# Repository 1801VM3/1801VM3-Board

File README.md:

# 1801VM3-Board
# 1801VM3-Board

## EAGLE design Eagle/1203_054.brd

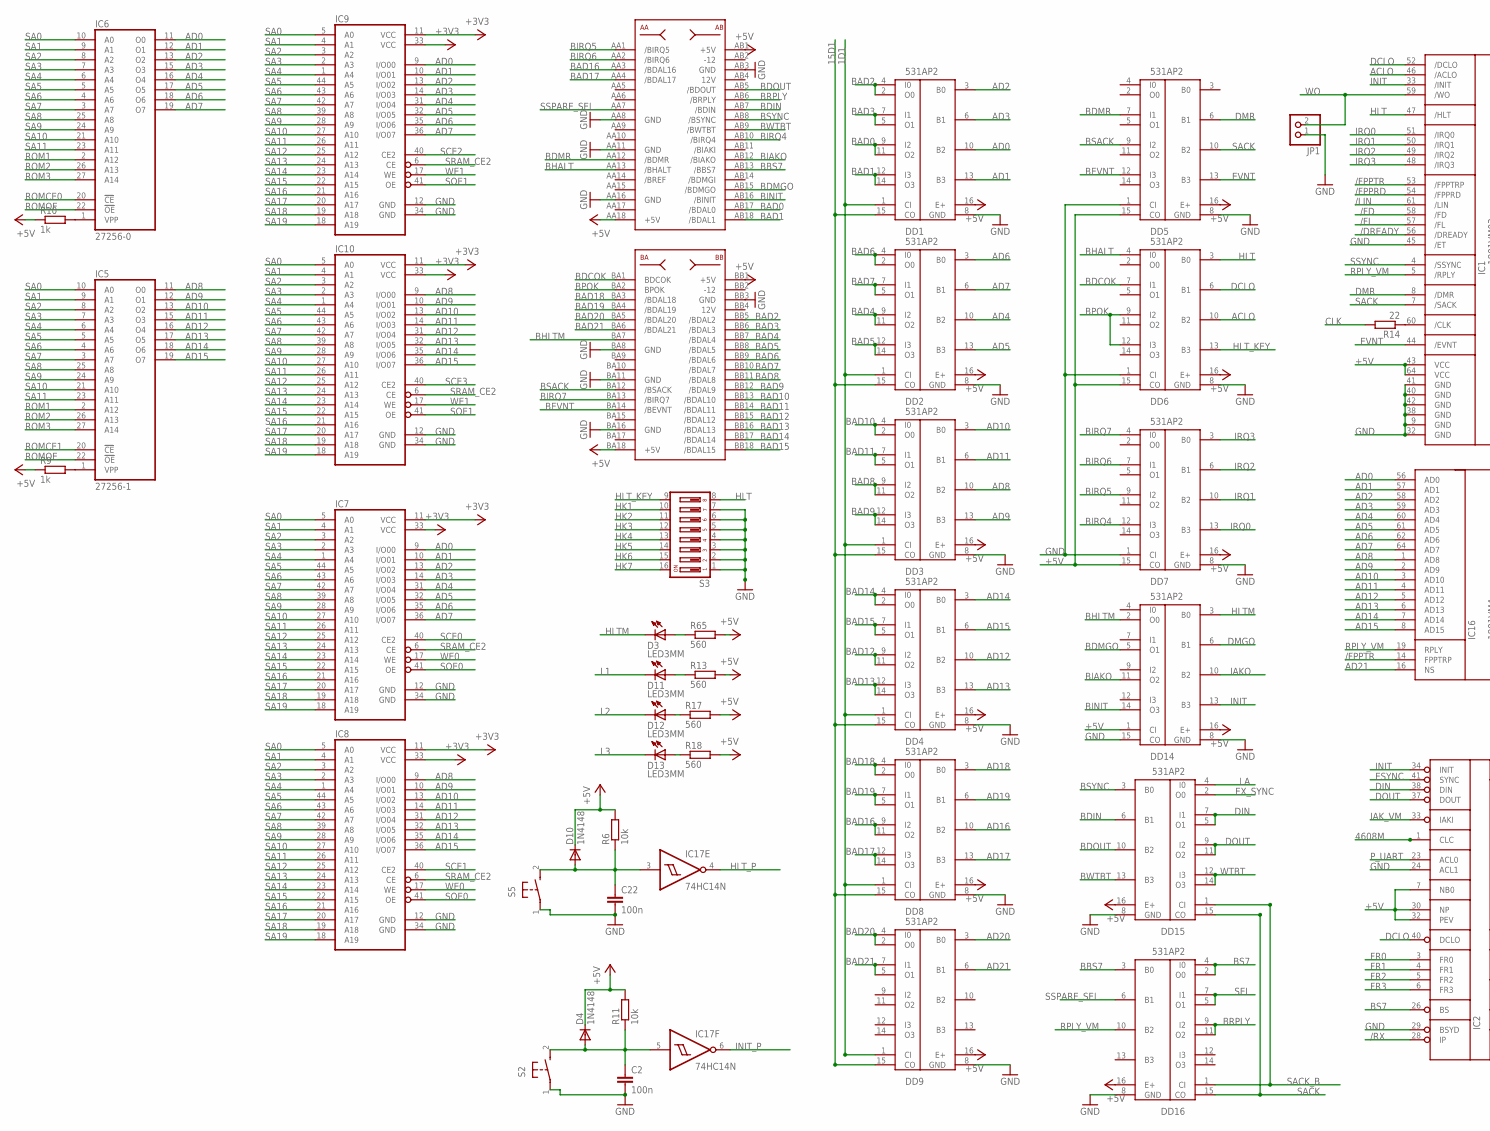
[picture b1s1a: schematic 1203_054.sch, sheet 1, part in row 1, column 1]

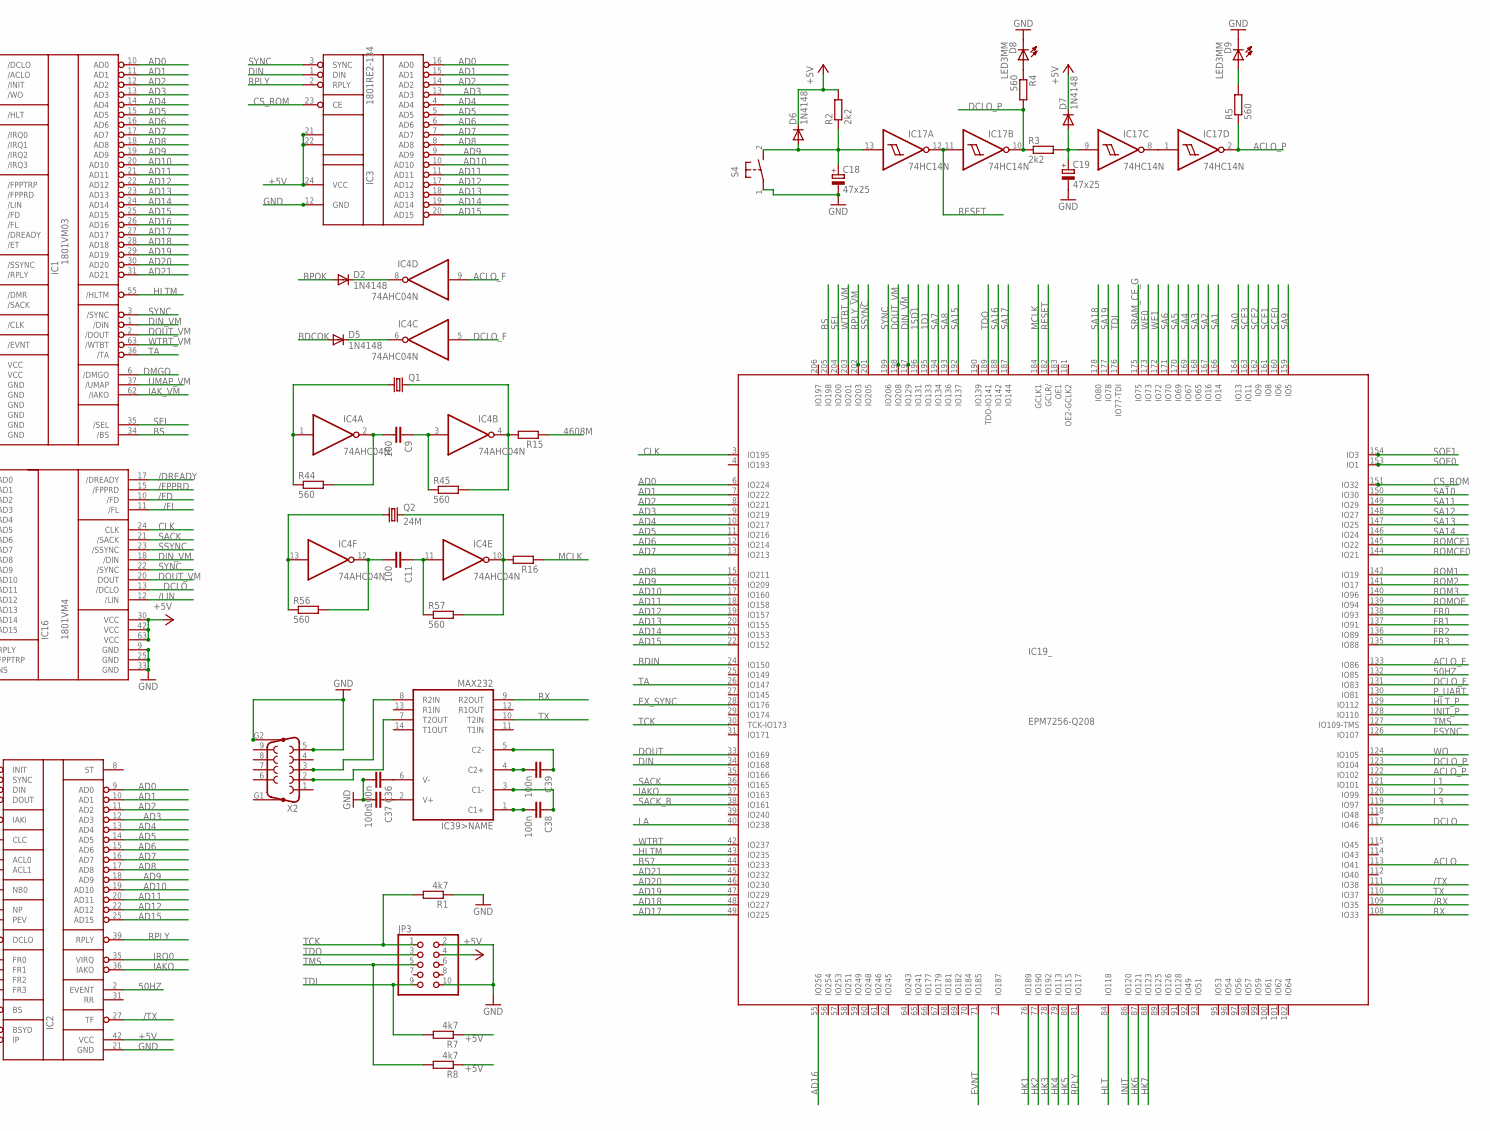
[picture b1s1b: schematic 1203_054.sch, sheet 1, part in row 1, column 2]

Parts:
C2, C22: 100n; C050-024X044
C9, C11: 100; C025-024X044
C18, C19: 47x25; E2,5-5
C36, C37, C38, C39: 100n; C025-024X044
D2, D4, D5, D6, D7, D10: 1N4148; DO35-10
D3, D8, D9, D11, D12, D13: LED3MM
DD1, DD2, DD3, DD4, DD5, DD6, DD7, DD8, DD9, DD14, DD15, DD16: 531AP2; DIL16
IC1: 1801VM03; DIL64
IC2: 1801VP1-065; 1801
IC3: 1801RE2-134; DIL24
IC4: 74AHC04N; DIL14
IC5: 27256-1; DIL28
IC6: 27256-0; DIL28
IC7, IC8, IC9, IC10: AS6C800855Z; TSOP44
IC16: 1801VM4
IC17: 74HC14N; DIL14
IC19: EPM7256-Q208; RQFP208
IC39: MAX232; DIL16
JP1: PINHD-1X2; 1X02
JP3: PINHD-2X5; 2X05
Q1: HC49U70
Q2: 24M; HC49U70
R1, R7, R8: 4k7; M0805
R2, R3: 2k2; 0207/10
R4, R5, R13, R17, R18, R65: 560; M0805
R6, R11: 10k; 0207/10
R9, R10: 1k; M0805
R14: 22; 0204V
R15, R16: R-EU_0204/2V; 0204V
R44, R45, R56, R57: 560; 0204V
S2, S4, S5: 31-XX; B3F-31XX
S3: DP08; DP-08
X2: F09HP
XP1: CON1

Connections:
1D1: DD1.1 (CI), DD2.1 (CI), DD3.1 (CI), DD4.1 (CI), DD8.1 (CI), DD9.1 (CI), IC19.195 (IO133); also elsewhere on the board
15D1: DD1.15 (CO), DD2.15 (CO), DD3.15 (CO), DD4.15 (CO), DD8.15 (CO), DD9.15 (CO), IC19.196 (IO131)
50HZ: IC2.2 (EVENT), IC19.132 (IO85)
4608M: IC2.1 (CLC), R15.1
4608MM: IC4.10 (O), Q2.2, R16.2, R57.2
+3V3: IC7.11 (VCC), IC7.33 (VCC), IC8.11 (VCC), IC8.33 (VCC), IC9.11 (VCC), IC9.33 (VCC), IC10.11 (VCC), IC10.33 (VCC); also elsewhere on the board
+5V: D4.K (C), D6.K (C), D7.K (C), D10.K (C), DD1.16 (E+), DD2.16 (E+), DD3.16 (E+), DD4.16 (E+), DD5.15 (CO), DD5.16 (E+), DD6.15 (CO), DD6.16 (E+), DD7.15 (CO), DD7.16 (E+), DD8.16 (E+), DD9.16 (E+), DD14.1 (CI), DD14.16 (E+), DD15.16 (E+), DD16.16 (E+), IC1.43 (VCC), IC1.64 (VCC), IC2.7 (NB0), IC2.30 (NP), IC2.32 (PEV), IC2.42 (VCC), IC3.21 (F0), IC3.22 (F1), IC3.24 (VCC), IC4.14 (VCC), IC5.28 (VCC), IC6.28 (VCC), IC16.30 (VCC), IC16.42 (VCC), IC16.63 (VCC), IC17.14 (VCC), IC19.83 (VCC), IC19.179 (VCC), IC19.186 (VCC), JP3.4, R2.2, R6.2, R7.1, R8.1, R9.1, R10.1, R11.2, R13.2, R17.2, R18.2, R65.2, XP1.AA18 (+5V), XP1.AB1 (+5V), XP1.BA18 (+5V), XP1.BB1 (+5V); also elsewhere on the board
/DREADY: IC1.56 (/DREADY), IC16.17 (/DREADY); also elsewhere on the board
/FD: IC1.58 (/FD), IC16.10 (/FD); also elsewhere on the board
/FL: IC1.57 (/FL), IC16.11 (/FL); also elsewhere on the board
/FPPRD: IC1.54 (/FPPRD), IC16.15 (/FPPRD); also elsewhere on the board
/FPPTR: IC1.53 (/FPPTRP), IC16.14 (FPPTRP); also elsewhere on the board
/LIN: IC1.61 (/LIN), IC16.12 (/LIN); also elsewhere on the board
/RX: IC2.28 (IP), IC19.109 (IO35)
/TX: IC2.27 (TF), IC19.111 (IO38)
ACLO: DD6.10 (B2), IC1.46 (/ACLO), IC19.113 (IO41); also elsewhere on the board
ACLO_F: IC4.9 (I), IC19.133 (IO86)
ACLO_P: IC17.2 (O), IC19.122 (IO102), R5.1
AD0: DD1.10 (B2), IC1.10 (AD0), IC2.9 (AD0), IC3.16 (AD0), IC6.11 (O0), IC7.9 (I/O00), IC9.9 (I/O00), IC16.56 (AD0), IC19.6 (IO224); also elsewhere on the board
AD1: DD1.13 (B3), IC1.11 (AD1), IC2.10 (AD1), IC3.15 (AD1), IC6.12 (O1), IC7.10 (I/O01), IC9.10 (I/O01), IC16.57 (AD1), IC19.7 (IO222); also elsewhere on the board
AD2: DD1.3 (B0), IC1.12 (AD2), IC2.11 (AD2), IC3.14 (AD2), IC6.13 (O2), IC7.13 (I/O02), IC9.13 (I/O02), IC16.58 (AD2), IC19.8 (IO221); also elsewhere on the board
AD3: DD1.6 (B1), IC1.13 (AD3), IC2.12 (AD3), IC3.13 (AD3), IC6.15 (O3), IC7.14 (I/O03), IC9.14 (I/O03), IC16.59 (AD3), IC19.9 (IO219); also elsewhere on the board
AD4: DD2.10 (B2), IC1.14 (AD4), IC2.13 (AD4), IC3.4 (AD4), IC6.16 (O4), IC7.31 (I/O04), IC9.31 (I/O04), IC16.60 (AD4), IC19.10 (IO217); also elsewhere on the board
AD5: DD2.13 (B3), IC1.15 (AD5), IC2.14 (AD5), IC3.5 (AD5), IC6.17 (O5), IC7.32 (I/O05), IC9.32 (I/O05), IC16.61 (AD5), IC19.11 (IO216); also elsewhere on the board
AD6: DD2.3 (B0), IC1.16 (AD6), IC2.15 (AD6), IC3.6 (AD6), IC6.18 (O6), IC7.35 (I/O06), IC9.35 (I/O06), IC16.62 (AD6), IC19.12 (IO214); also elsewhere on the board
AD7: DD2.6 (B1), IC1.17 (AD7), IC2.16 (AD7), IC3.7 (AD7), IC6.19 (O7), IC7.36 (I/O07), IC9.36 (I/O07), IC16.64 (AD7), IC19.13 (IO213); also elsewhere on the board
AD8: DD3.10 (B2), IC1.18 (AD8), IC2.17 (AD8), IC3.8 (AD8), IC5.11 (O0), IC8.9 (I/O00), IC10.9 (I/O00), IC16.1 (AD8), IC19.15 (IO211); also elsewhere on the board
AD9: DD3.13 (B3), IC1.19 (AD9), IC2.18 (AD9), IC3.9 (AD9), IC5.12 (O1), IC8.10 (I/O01), IC10.10 (I/O01), IC16.2 (AD9), IC19.16 (IO209); also elsewhere on the board
AD10: DD3.3 (B0), IC1.20 (AD10), IC2.19 (AD10), IC3.10 (AD10), IC5.13 (O2), IC8.13 (I/O02), IC10.13 (I/O02), IC16.3 (AD10), IC19.17 (IO160); also elsewhere on the board
AD11: DD3.6 (B1), IC1.21 (AD11), IC2.20 (AD11), IC3.11 (AD11), IC5.15 (O3), IC8.14 (I/O03), IC10.14 (I/O03), IC16.4 (AD11), IC19.18 (IO158); also elsewhere on the board
AD12: DD4.10 (B2), IC1.22 (AD12), IC2.22 (AD12), IC3.17 (AD12), IC5.16 (O4), IC8.31 (I/O04), IC10.31 (I/O04), IC16.5 (AD12), IC19.19 (IO157); also elsewhere on the board
AD13: DD4.13 (B3), IC1.23 (AD13), IC3.18 (AD13), IC5.17 (O5), IC8.32 (I/O05), IC10.32 (I/O05), IC16.6 (AD13), IC19.20 (IO155); also elsewhere on the board
AD14: DD4.3 (B0), IC1.24 (AD14), IC3.19 (AD14), IC5.18 (O6), IC8.35 (I/O06), IC10.35 (I/O06), IC16.7 (AD14), IC19.21 (IO153); also elsewhere on the board
AD15: DD4.6 (B1), IC1.25 (AD15), IC2.25 (AD15), IC3.20 (AD15), IC5.19 (O7), IC8.36 (I/O07), IC10.36 (I/O07), IC16.8 (AD15), IC19.22 (IO152); also elsewhere on the board
AD16: DD8.10 (B2), IC1.26 (AD16), IC19.55 (IO256); also elsewhere on the board
AD17: DD8.13 (B3), IC1.27 (AD17), IC19.49 (IO225); also elsewhere on the board
AD18: DD8.3 (B0), IC1.28 (AD18), IC19.48 (IO227); also elsewhere on the board
AD19: DD8.6 (B1), IC1.29 (AD19), IC19.47 (IO229); also elsewhere on the board
AD20: DD9.3 (B0), IC1.30 (AD20), IC19.46 (IO230); also elsewhere on the board
AD21: DD9.6 (B1), IC1.31 (AD21), IC16.16 (NS), IC19.45 (IO232); also elsewhere on the board
BAD0: DD1.9 (I2), DD1.11 (O2), XP1.AB17 (/BDAL0); also elsewhere on the board
BAD1: DD1.12 (I3), DD1.14 (O3), XP1.AB18 (/BDAL1); also elsewhere on the board
BAD2: DD1.2 (O0), DD1.4 (I0), XP1.BB5 (/BDAL2); also elsewhere on the board
BAD3: DD1.5 (O1), DD1.7 (I1), XP1.BB6 (/BDAL3); also elsewhere on the board
BAD4: DD2.9 (I2), DD2.11 (O2), XP1.BB7 (/BDAL4); also elsewhere on the board
BAD5: DD2.12 (I3), DD2.14 (O3), XP1.BB8 (/BDAL5); also elsewhere on the board
BAD6: DD2.2 (O0), DD2.4 (I0), XP1.BB9 (/BDAL6); also elsewhere on the board
BAD7: DD2.5 (O1), DD2.7 (I1), XP1.BB10 (/BDAL7); also elsewhere on the board
BAD8: DD3.9 (I2), DD3.11 (O2), XP1.BB11 (/BDAL8); also elsewhere on the board
BAD9: DD3.12 (I3), DD3.14 (O3), XP1.BB12 (/BDAL9); also elsewhere on the board
BAD10: DD3.2 (O0), DD3.4 (I0), XP1.BB13 (/BDAL10); also elsewhere on the board
BAD11: DD3.5 (O1), DD3.7 (I1), XP1.BB14 (/BDAL11); also elsewhere on the board
BAD12: DD4.9 (I2), DD4.11 (O2), XP1.BB15 (/BDAL12); also elsewhere on the board
BAD13: DD4.12 (I3), DD4.14 (O3), XP1.BB16 (/BDAL13); also elsewhere on the board
BAD14: DD4.2 (O0), DD4.4 (I0), XP1.BB17 (/BDAL14); also elsewhere on the board
BAD15: DD4.5 (O1), DD4.7 (I1), XP1.BB18 (/BDAL15); also elsewhere on the board
BAD16: DD8.9 (I2), DD8.11 (O2), XP1.AA3 (/BDAL16); also elsewhere on the board
BAD17: DD8.12 (I3), DD8.14 (O3), XP1.AA4 (/BDAL17); also elsewhere on the board
BAD18: DD8.2 (O0), DD8.4 (I0), XP1.BA3 (/BDAL18); also elsewhere on the board
BAD19: DD8.5 (O1), DD8.7 (I1), XP1.BA4 (/BDAL19); also elsewhere on the board
BAD20: DD9.2 (O0), DD9.4 (I0), XP1.BA5 (/BDAL20); also elsewhere on the board
BAD21: DD9.5 (O1), DD9.7 (I1), XP1.BA6 (/BDAL21); also elsewhere on the board
BBS7: DD16.3 (B0), XP1.AB13 (/BBS7); also elsewhere on the board
BDCOK: D5.A, DD6.7 (I1), XP1.BA1 (BDCOK); also elsewhere on the board
BDIN: DD15.6 (B1), IC19.24 (IO150), XP1.AB7 (/BDIN); also elsewhere on the board
BDMGO: DD14.5 (O1), XP1.AB15 (/BDMGO); also elsewhere on the board
BDMR: DD5.7 (I1), XP1.AA12 (/BDMR); also elsewhere on the board
BDOUT: DD15.10 (B2), XP1.AB5 (/BDOUT); also elsewhere on the board
BEVNT: DD5.12 (I3), XP1.BA14 (/BEVNT); also elsewhere on the board
BHALT: DD6.4 (I0), XP1.AA13 (/BHALT); also elsewhere on the board
BHLTM: DD14.2 (O0), XP1.BA7; also elsewhere on the board
BIAKO: DD14.11 (O2), XP1.AB12 (/BIAKO); also elsewhere on the board
BINIT: DD14.14 (O3), XP1.AB16 (/BINIT); also elsewhere on the board
BIRQ4: DD7.12 (I3), XP1.AB10 (/BIRQ4); also elsewhere on the board
BIRQ5: DD7.9 (I2), XP1.AA1 (/BIRQ5); also elsewhere on the board
BIRQ6: DD7.7 (I1), XP1.AA2 (/BIRQ6); also elsewhere on the board
BIRQ7: DD7.4 (I0), XP1.BA13 (/BIRQ7); also elsewhere on the board
BPOK: D2.A, DD6.9 (I2), DD6.12 (I3), XP1.BA2 (BPOK); also elsewhere on the board
BRPLY: DD16.9 (I2), DD16.11 (O2), XP1.AB6 (/BRPLY); also elsewhere on the board
BS: IC1.34 (/BS), IC19.205 (IO198); also elsewhere on the board
BS7: DD16.2 (O0), DD16.4 (I0), IC2.26 (BS), IC19.44 (IO233); also elsewhere on the board
BSACK: DD5.9 (I2), XP1.BA12 (/BSACK); also elsewhere on the board
BSYNC: DD15.3 (B0), XP1.AB8 (/BSYNC); also elsewhere on the board
BWTBT: DD15.13 (B3), XP1.AB9 (/BWTBT); also elsewhere on the board
CLK: IC16.24 (CLK), IC19.3 (IO195), R14.2
CS_ROM: IC3.23 (CE), IC19.151 (IO32)
DCLO: DD6.6 (B1), IC1.52 (/DCLO), IC2.40 (DCLO), IC16.13 (/DCLO), IC19.117 (IO46); also elsewhere on the board
DCLO_F: IC4.5 (I), IC19.131 (IO83)
DCLO_P: IC17.10 (O), IC19.123 (IO104), R3.1, R4.2
DIN: DD15.5 (O1), DD15.7 (I1), IC2.38 (DIN), IC3.1 (DIN), IC19.34 (IO168); also elsewhere on the board
DIN_VM: IC1.1 (/DIN), IC16.18 (/DIN), IC19.197 (IO129); also elsewhere on the board
DMGO: DD14.6 (B1), IC1.6 (/DMGO); also elsewhere on the board
DMR: DD5.6 (B1), IC1.8 (/DMR); also elsewhere on the board
DOUT: DD15.9 (I2), DD15.11 (O2), IC2.37 (DOUT), IC19.33 (IO169); also elsewhere on the board
DOUT_VM: IC1.2 (/DOUT), IC16.20 (DOUT), IC19.198 (IO208); also elsewhere on the board
ESYNC: IC2.41 (SYNC), IC19.126 (IO107)
EVNT: DD5.13 (B3), IC1.44 (/EVNT), IC19.71 (IO185); also elsewhere on the board
EX_SYNC: DD15.2 (O0), IC19.28 (IO176); also elsewhere on the board
FR0: IC2.3 (FR0), IC19.138 (IO93)
FR1: IC2.4 (FR1), IC19.137 (IO91)
FR2: IC2.5 (FR2), IC19.136 (IO89)
FR3: IC2.6 (FR3), IC19.135 (IO88)
GND: C2.2, C18.-, C19.-, C22.2, C36.2, C37.2, D8.K (C), D9.K (C), DD1.8 (GND), DD2.8 (GND), DD3.8 (GND), DD4.8 (GND), DD5.1 (CI), DD5.8 (GND), DD6.1 (CI), DD6.8 (GND), DD7.1 (CI), DD7.8 (GND), DD8.8 (GND), DD9.8 (GND), DD14.8 (GND), DD14.15 (CO), DD15.8 (GND), DD16.8 (GND), IC1.9 (GND), IC1.32 (GND), IC1.38 (GND), IC1.40 (GND), IC1.41 (GND), IC1.42 (GND), IC1.45 (/ET), IC2.21 (GND), IC2.24 (ACL1), IC2.29 (BSYD), IC3.12 (GND), IC4.7 (GND), IC5.14 (GND), IC6.14 (GND), IC7.12 (GND), IC7.34 (GND), IC8.12 (GND), IC8.34 (GND), IC9.12 (GND), IC9.34 (GND), IC10.12 (GND), IC10.34 (GND), IC16.9 (GND), IC16.25 (GND), IC16.33 (GND), IC17.7 (GND), JP1.1, JP3.2, JP3.10, R1.1, S2.1, S3.1, S3.2, S3.3, S3.4, S3.5, S3.6, S3.7, S4.1, S5.1, X2.5, X2.G2, XP1.AA8 (GND), XP1.AA11 (GND), XP1.AA16 (GND), XP1.AB3 (GND), XP1.BA8 (GND), XP1.BA11 (GND), XP1.BA16 (GND), XP1.BB3 (GND); also elsewhere on the board
HK1: IC19.76 (IO189), S3.10; also elsewhere on the board
HK2: IC19.77 (IO190), S3.11; also elsewhere on the board
HK3: IC19.78 (IO192), S3.12; also elsewhere on the board
HK4: IC19.79 (IO113), S3.13; also elsewhere on the board
HK5: IC19.80 (IO115), S3.14; also elsewhere on the board
HK6: IC19.87 (IO121), S3.15; also elsewhere on the board
HK7: IC19.88 (IO123), S3.16; also elsewhere on the board
HLT: DD6.3 (B0), IC1.47 (/HLT), IC19.84 (IO118), S3.8; also elsewhere on the board
HLTM: D3.K (C), DD14.3 (B0), IC1.55 (/HLTM), IC19.43 (IO235); also elsewhere on the board
HLT_KEY: DD6.13 (B3), S3.9
HLT_P: IC17.4 (O), IC19.129 (IO112)
IAKO: DD14.10 (B2), IC2.36 (IAKO), IC19.37 (IO163)
IAK_VM: IC1.62 (/IAKO), IC2.33 (IAKI); also elsewhere on the board
INIT: DD14.13 (B3), IC1.33 (/INIT), IC2.34 (INIT), IC19.86 (IO120); also elsewhere on the board
INIT_P: IC17.6 (O), IC19.128 (IO110)
IRQ0: DD7.13 (B3), IC1.51 (/IRQ0), IC2.35 (VIRQ); also elsewhere on the board
IRQ1: DD7.10 (B2), IC1.50 (/IRQ1); also elsewhere on the board
IRQ2: DD7.6 (B1), IC1.49 (/IRQ2); also elsewhere on the board
IRQ3: DD7.3 (B0), IC1.48 (/IRQ3); also elsewhere on the board
L1: D11.K (C), IC19.121 (IO101)
L2: D12.K (C), IC19.120 (IO99)
L3: D13.K (C), IC19.119 (IO97)
LA: DD15.4 (I0), IC19.40 (IO238)
MCLK: IC19.184 (GCLK1), R16.1
MCLKK: IC4.4 (O), Q1.2, R15.2, R45.2
unnamed: IC6.1 (VPP), R10.2
unnamed: IC17.1 (I), IC17.8 (O)
unnamed: C38.1, IC39.3 (C1-)
unnamed: D9.A, R5.2
unnamed: C18.+, D6.A, IC17.13 (I), R2.1, S4.2
unnamed: IC4.1 (I), Q1.1, R44.1
unnamed: D3.A, R65.1
unnamed: C9.2, IC4.2 (O), R44.2
unnamed: C19.+, D7.A, IC17.9 (I), R3.2
unnamed: D8.A, R4.1
unnamed: IC5.1 (VPP), R9.2
unnamed: C22.1, D10.A, IC17.3 (I), R6.1, S5.2
unnamed: D11.A, R13.1
unnamed: IC1.60 (/CLK), R14.1
unnamed: D2.K (C), IC4.8 (O)
unnamed: D5.K (C), IC4.6 (O)
unnamed: C2.1, D4.A, IC17.5 (I), R11.1, S2.2
unnamed: D12.A, R17.1
unnamed: D13.A, R18.1
unnamed: IC4.13 (I), Q2.1, R56.1
unnamed: C9.1, IC4.3 (I), R45.1
unnamed: C38.2, IC39.1 (C1+)
unnamed: C39.2, IC39.4 (C2+)
unnamed: C39.1, IC39.5 (C2-)
unnamed: IC39.7 (T2OUT), X2.2
unnamed: IC39.8 (R2IN), X2.3
unnamed: C36.1, IC39.6 (V-)
unnamed: C37.1, IC39.2 (V+)
unnamed: C11.2, IC4.12 (O), R56.2
unnamed: C11.1, IC4.11 (I), R57.1
P_UART: IC2.23 (ACL0), IC19.130 (IO81)
RESET: IC17.11 (I), IC17.12 (O), IC19.182 (GCLR/)
ROM1: IC5.2 (A12), IC6.2 (A12), IC19.142 (IO19)
ROM2: IC5.26 (A13), IC6.26 (A13), IC19.141 (IO17)
ROM3: IC5.27 (A14), IC6.27 (A14), IC19.140 (IO96)
ROMCE0: IC6.20 (!CE), IC19.144 (IO21)
ROMCE1: IC5.20 (!CE), IC19.145 (IO22)
ROMOE: IC5.22 (!OE), IC6.22 (!OE), IC19.139 (IO94)
RPLY: IC2.39 (RPLY), IC3.2 (RPLY), IC19.81 (IO117); also elsewhere on the board
RPLY_VM: DD16.10 (B2), IC1.5 (/RPLY), IC16.19 (RPLY), IC19.202 (IO203); also elsewhere on the board
RX: IC19.108 (IO33), IC39.9 (R2OUT)
SA0: IC5.10 (A0), IC6.10 (A0), IC7.5 (A0), IC8.5 (A0), IC9.5 (A0), IC10.5 (A0), IC19.164 (IO13)
SA1: IC5.9 (A1), IC6.9 (A1), IC7.4 (A1), IC8.4 (A1), IC9.4 (A1), IC10.4 (A1), IC19.166 (IO14)
SA2: IC5.8 (A2), IC6.8 (A2), IC7.3 (A2), IC8.3 (A2), IC9.3 (A2), IC10.3 (A2), IC19.167 (IO16)
SA3: IC5.7 (A3), IC6.7 (A3), IC7.2 (A3), IC8.2 (A3), IC9.2 (A3), IC10.2 (A3), IC19.168 (IO65)
SA4: IC5.6 (A4), IC6.6 (A4), IC7.1 (A4), IC8.1 (A4), IC9.1 (A4), IC10.1 (A4), IC19.169 (IO67)
SA5: IC5.5 (A5), IC6.5 (A5), IC7.44 (A5), IC8.44 (A5), IC9.44 (A5), IC10.44 (A5), IC19.170 (IO69)
SA6: IC5.4 (A6), IC6.4 (A6), IC7.43 (A6), IC8.43 (A6), IC9.43 (A6), IC10.43 (A6), IC19.171 (IO70)
SA7: IC5.3 (A7), IC6.3 (A7), IC7.42 (A7), IC8.42 (A7), IC9.42 (A7), IC10.42 (A7), IC19.194 (IO134)
SA8: IC5.25 (A8), IC6.25 (A8), IC7.39 (A8), IC8.39 (A8), IC9.39 (A8), IC10.39 (A8), IC19.193 (IO136)
SA9: IC5.24 (A9), IC6.24 (A9), IC7.28 (A9), IC8.28 (A9), IC9.28 (A9), IC10.28 (A9), IC19.159 (IO5)
SA10: IC5.21 (A10), IC6.21 (A10), IC7.27 (A10), IC8.27 (A10), IC9.27 (A10), IC10.27 (A10), IC19.150 (IO30)
SA11: IC5.23 (A11), IC6.23 (A11), IC7.26 (A11), IC8.26 (A11), IC9.26 (A11), IC10.26 (A11), IC19.149 (IO29)
SA12: IC7.25 (A12), IC8.25 (A12), IC9.25 (A12), IC10.25 (A12), IC19.148 (IO27)
SA13: IC7.24 (A13), IC8.24 (A13), IC9.24 (A13), IC10.24 (A13), IC19.147 (IO25)
SA14: IC7.23 (A14), IC8.23 (A14), IC9.23 (A14), IC10.23 (A14), IC19.146 (IO24)
SA15: IC7.22 (A15), IC8.22 (A15), IC9.22 (A15), IC10.22 (A15), IC19.192 (IO137)
SA16: IC7.21 (A16), IC8.21 (A16), IC9.21 (A16), IC10.21 (A16), IC19.188 (IO142)
SA17: IC7.20 (A17), IC8.20 (A17), IC9.20 (A17), IC10.20 (A17), IC19.187 (IO144)
SA18: IC7.19 (A18), IC8.19 (A18), IC9.19 (A18), IC10.19 (A18), IC19.178 (IO80)
SA19: IC7.18 (A19), IC8.18 (A19), IC9.18 (A19), IC10.18 (A19), IC19.177 (IO78)
SACK: DD5.10 (B2), DD15.15 (CO), DD16.15 (CO), IC1.7 (/SACK), IC16.21 (/SACK), IC19.36 (IO165); also elsewhere on the board
SACK_B: DD15.1 (CI), DD16.1 (CI), IC19.38 (IO161)
SCE0: IC7.40 (CE2), IC19.160 (IO6)
SCE1: IC8.40 (CE2), IC19.161 (IO8)
SCE2: IC9.40 (CE2), IC19.162 (IO9)
SCE3: IC10.40 (CE2), IC19.163 (IO11)
SEL: DD16.5 (O1), DD16.7 (I1), IC1.35 (/SEL), IC19.204 (IO200); also elsewhere on the board
SOE0: IC7.41 (OE), IC8.41 (OE), IC19.153 (IO1)
SOE1: IC9.41 (OE), IC10.41 (OE), IC19.154 (IO3)
SRAM_CE2: IC7.6 (CE), IC8.6 (CE), IC9.6 (CE), IC10.6 (CE); also elsewhere on the board
SRAM_CE_G: IC19.175 (IO75); also elsewhere on the board
SSPARE_SEL: DD16.6 (B1), XP1.AA7; also elsewhere on the board
SSYNC: IC1.4 (/SSYNC), IC16.23 (/SSYNC), IC19.201 (IO205); also elsewhere on the board
SYNC: IC1.3 (/SYNC), IC3.3 (SYNC), IC16.22 (/SYNC), IC19.199 (IO206); also elsewhere on the board
TA: IC1.36 (/TA), IC19.26 (IO147); also elsewhere on the board
TCK: IC19.30 (TCK-IO173), JP3.1, R1.2
TDI: IC19.176 (IO77-TDI), JP3.9, R7.2
TDO: IC19.189 (TDO-IO141), JP3.3
TMS: IC19.127 (IO109-TMS), JP3.5, R8.2
TX: IC19.110 (IO37), IC39.10 (T2IN)
UMAP_VM: IC1.37 (/UMAP); also elsewhere on the board
WE0: IC7.17 (WE), IC8.17 (WE), IC19.173 (IO73)
WE1: IC9.17 (WE), IC10.17 (WE), IC19.172 (IO72)
WO: IC1.59 (/WO), IC19.124 (IO105), JP1.2; also elsewhere on the board
WTBT: DD15.12 (I3), DD15.14 (O3), IC19.42 (IO237); also elsewhere on the board
WTBT_VM: IC1.63 (/WTBT), IC19.203 (IO201); also elsewhere on the board

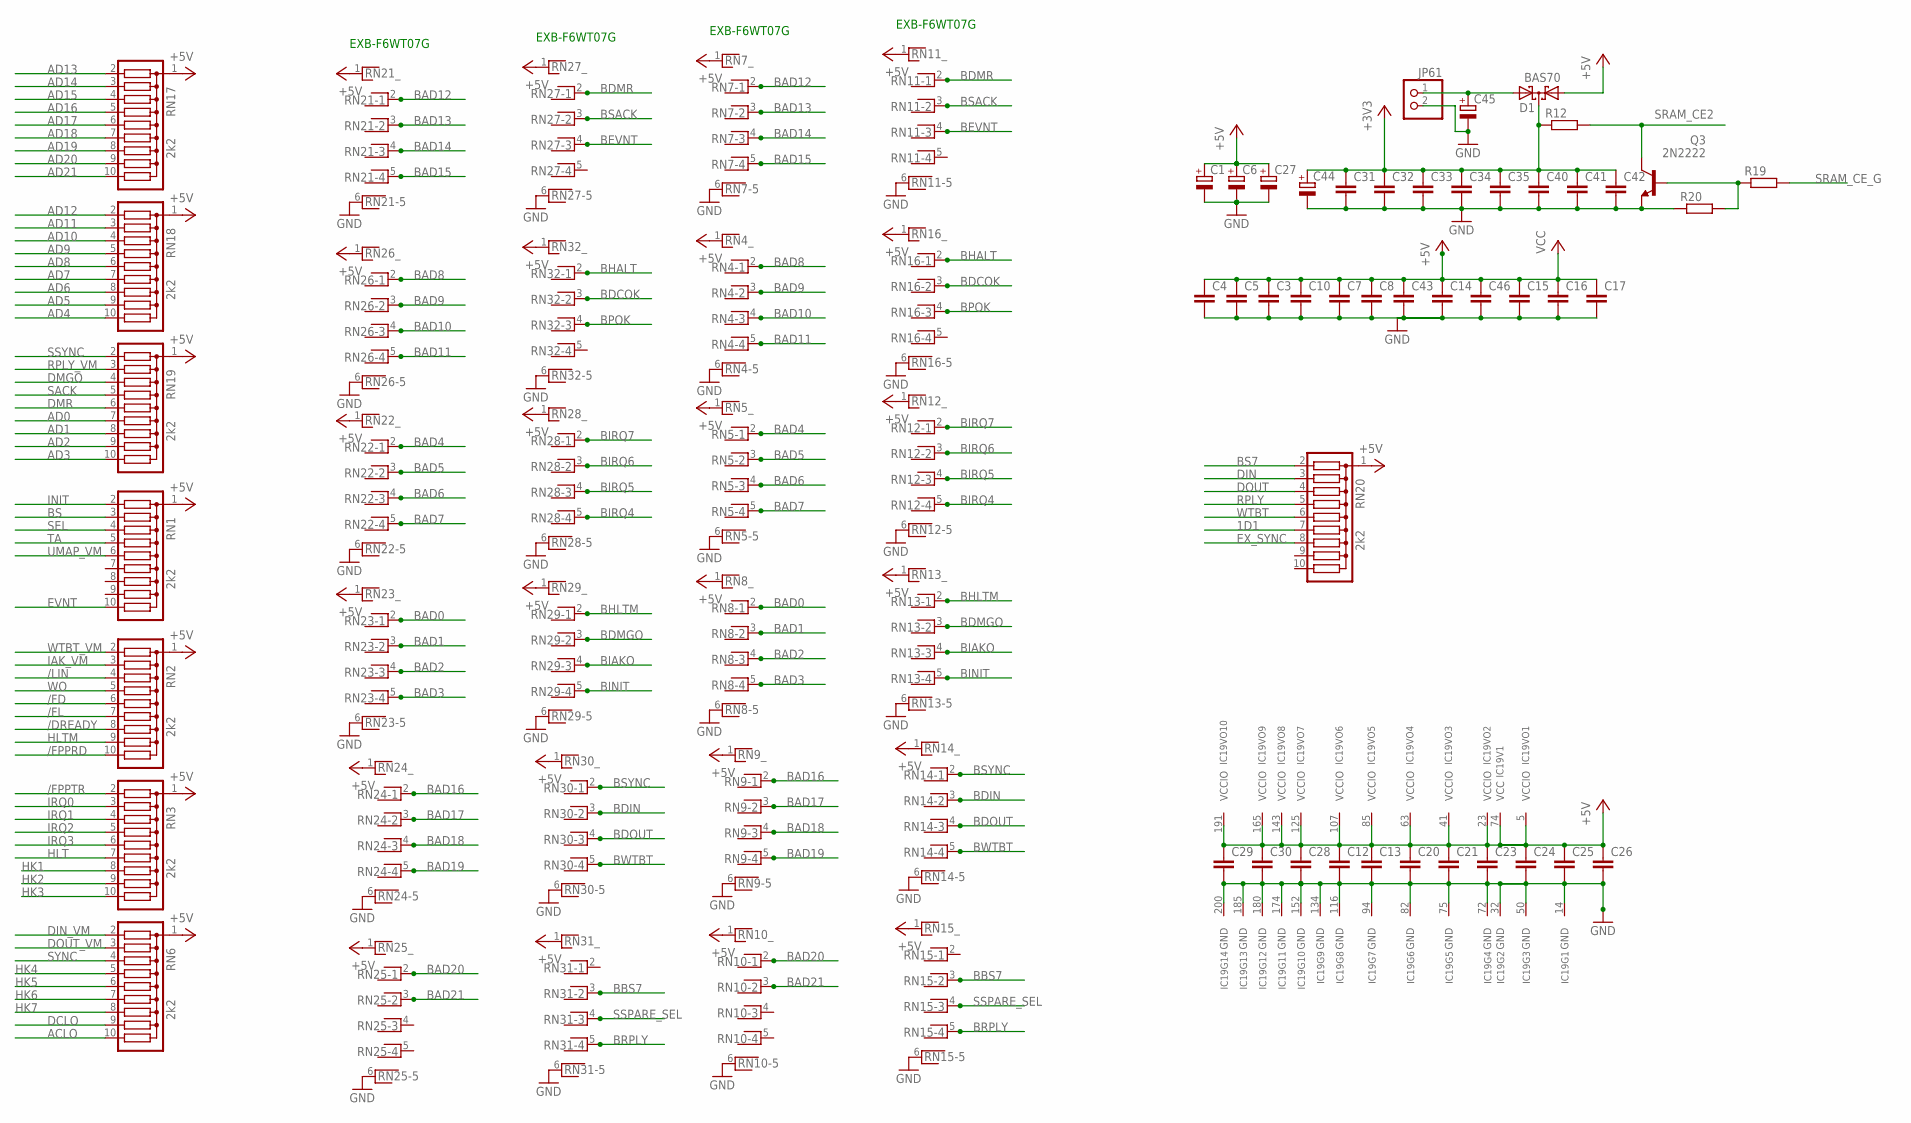
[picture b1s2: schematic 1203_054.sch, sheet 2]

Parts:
C1, C6, C27: CPOL-EUCT6032; CT6032
C3, C4, C5, C7, C8, C10, C14, C15, C16, C17, C23, C24, C25, C26, C28, C29, C30, C43, C46: C-EU050-024X044; C050-024X044
C12, C13, C20, C21: C-EUC0805; C0805
C31, C32, C33, C34, C35, C40, C41, C42: C-EUC0603; C0603
C44, C45: CPOL-EUCT7343; CT7343
D1: BAS70; SOT23
IC19: EPM7256-Q208; RQFP208
JP61: PINHD-1X2; 1X02
Q3: 2N2222; TO18
R12, R19, R20: R-EU_M0805; M0805
RN1, RN2, RN3, RN6, RN17, RN18, RN19, RN20: 2k2; SIL10
RN4, RN5, RN7, RN8, RN9, RN10, RN11, RN12, RN13, RN14, RN15, RN16, RN21, RN22, RN23, RN24, RN25, RN26, RN27, RN28, RN29, RN30, RN31, RN32: RNX5; RN-6

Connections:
1D1: RN20.7; also elsewhere on the board
+3V3: C31.1, C32.1, C33.1, C34.1, C35.1, C40.1, C41.1, C42.1, C44.+, D1.3 (C), R12.1; also elsewhere on the board
+5V: C1.+, C3.1, C4.1, C5.1, C6.+, C7.1, C8.1, C10.1, C12.1, C13.1, C14.1, C15.1, C16.1, C17.1, C20.1, C21.1, C23.1, C24.1, C25.1, C26.1, C27.+, C28.1, C29.1, C30.1, C43.1, C46.1, D1.1 (A1), IC19.5 (VCCIO), IC19.23 (VCCIO), IC19.41 (VCCIO), IC19.63 (VCCIO), IC19.74 (VCC), IC19.83 (VCC), IC19.85 (VCCIO), IC19.107 (VCCIO), IC19.125 (VCCIO), IC19.143 (VCCIO), IC19.165 (VCCIO), IC19.179 (VCC), IC19.186 (VCC), IC19.191 (VCCIO), RN1.1, RN2.1, RN3.1, RN4.1, RN5.1, RN6.1, RN7.1, RN8.1, RN9.1, RN10.1, RN11.1, RN12.1, RN13.1, RN14.1, RN15.1, RN16.1, RN17.1, RN18.1, RN19.1, RN20.1, RN21.1, RN22.1, RN23.1, RN24.1, RN25.1, RN26.1, RN27.1, RN28.1, RN29.1, RN30.1, RN31.1, RN32.1; also elsewhere on the board
/DREADY: RN2.8; also elsewhere on the board
/FD: RN2.6; also elsewhere on the board
/FL: RN2.7; also elsewhere on the board
/FPPRD: RN2.10; also elsewhere on the board
/FPPTR: RN3.2; also elsewhere on the board
/LIN: RN2.4; also elsewhere on the board
ACLO: RN6.10; also elsewhere on the board
AD0: RN19.7; also elsewhere on the board
AD1: RN19.8; also elsewhere on the board
AD2: RN19.9; also elsewhere on the board
AD3: RN19.10; also elsewhere on the board
AD4: RN18.10; also elsewhere on the board
AD5: RN18.9; also elsewhere on the board
AD6: RN18.8; also elsewhere on the board
AD7: RN18.7; also elsewhere on the board
AD8: RN18.6; also elsewhere on the board
AD9: RN18.5; also elsewhere on the board
AD10: RN18.4; also elsewhere on the board
AD11: RN18.3; also elsewhere on the board
AD12: RN18.2; also elsewhere on the board
AD13: RN17.2; also elsewhere on the board
AD14: RN17.3; also elsewhere on the board
AD15: RN17.4; also elsewhere on the board
AD16: RN17.5; also elsewhere on the board
AD17: RN17.6; also elsewhere on the board
AD18: RN17.7; also elsewhere on the board
AD19: RN17.8; also elsewhere on the board
AD20: RN17.9; also elsewhere on the board
AD21: RN17.10; also elsewhere on the board
BAD0: RN8.2, RN23.2; also elsewhere on the board
BAD1: RN8.3, RN23.3; also elsewhere on the board
BAD2: RN8.4, RN23.4; also elsewhere on the board
BAD3: RN8.5, RN23.5; also elsewhere on the board
BAD4: RN5.2, RN22.2; also elsewhere on the board
BAD5: RN5.3, RN22.3; also elsewhere on the board
BAD6: RN5.4, RN22.4; also elsewhere on the board
BAD7: RN5.5, RN22.5; also elsewhere on the board
BAD8: RN4.2, RN26.2; also elsewhere on the board
BAD9: RN4.3, RN26.3; also elsewhere on the board
BAD10: RN4.4, RN26.4; also elsewhere on the board
BAD11: RN4.5, RN26.5; also elsewhere on the board
BAD12: RN7.2, RN21.2; also elsewhere on the board
BAD13: RN7.3, RN21.3; also elsewhere on the board
BAD14: RN7.4, RN21.4; also elsewhere on the board
BAD15: RN7.5, RN21.5; also elsewhere on the board
BAD16: RN9.2, RN24.2; also elsewhere on the board
BAD17: RN9.3, RN24.3; also elsewhere on the board
BAD18: RN9.4, RN24.4; also elsewhere on the board
BAD19: RN9.5, RN24.5; also elsewhere on the board
BAD20: RN10.2, RN25.2; also elsewhere on the board
BAD21: RN10.3, RN25.3; also elsewhere on the board
BBS7: RN15.3, RN31.3; also elsewhere on the board
BDCOK: RN16.3, RN32.3; also elsewhere on the board
BDIN: RN14.3, RN30.3; also elsewhere on the board
BDMGO: RN13.3, RN29.3; also elsewhere on the board
BDMR: RN11.2, RN27.2; also elsewhere on the board
BDOUT: RN14.4, RN30.4; also elsewhere on the board
BEVNT: RN11.4, RN27.4; also elsewhere on the board
BHALT: RN16.2, RN32.2; also elsewhere on the board
BHLTM: RN13.2, RN29.2; also elsewhere on the board
BIAKO: RN13.4, RN29.4; also elsewhere on the board
BINIT: RN13.5, RN29.5; also elsewhere on the board
BIRQ4: RN12.5, RN28.5; also elsewhere on the board
BIRQ5: RN12.4, RN28.4; also elsewhere on the board
BIRQ6: RN12.3, RN28.3; also elsewhere on the board
BIRQ7: RN12.2, RN28.2; also elsewhere on the board
BPOK: RN16.4, RN32.4; also elsewhere on the board
BRPLY: RN15.5, RN31.5; also elsewhere on the board
BS: RN1.3; also elsewhere on the board
BS7: RN20.2; also elsewhere on the board
BSACK: RN11.3, RN27.3; also elsewhere on the board
BSYNC: RN14.2, RN30.2; also elsewhere on the board
BWTBT: RN14.5, RN30.5; also elsewhere on the board
DCLO: RN6.9; also elsewhere on the board
DIN: RN20.3; also elsewhere on the board
DIN_VM: RN6.2; also elsewhere on the board
DMGO: RN19.4; also elsewhere on the board
DMR: RN19.6; also elsewhere on the board
DOUT: RN20.4; also elsewhere on the board
DOUT_VM: RN6.3; also elsewhere on the board
EVNT: RN1.10; also elsewhere on the board
EX_SYNC: RN20.8; also elsewhere on the board
GND: C1.-, C3.2, C4.2, C5.2, C6.-, C7.2, C8.2, C10.2, C12.2, C13.2, C14.2, C15.2, C16.2, C17.2, C20.2, C21.2, C23.2, C24.2, C25.2, C26.2, C27.-, C28.2, C29.2, C30.2, C31.2, C32.2, C33.2, C34.2, C35.2, C40.2, C41.2, C42.2, C43.2, C44.-, C45.-, C46.2, IC19.14 (GND), IC19.32 (GND), IC19.50 (GND), IC19.72 (GND), IC19.75 (GND), IC19.82 (GND), IC19.94 (GND), IC19.116 (GND), IC19.134 (GND), IC19.152 (GND), IC19.174 (GND), IC19.180 (GND), IC19.185 (GND), IC19.200 (GND), JP61.2, Q3.1 (E), R20.1, RN4.6, RN5.6, RN7.6, RN8.6, RN9.6, RN10.6, RN11.6, RN12.6, RN13.6, RN14.6, RN15.6, RN16.6, RN21.6, RN22.6, RN23.6, RN24.6, RN25.6, RN26.6, RN27.6, RN28.6, RN29.6, RN30.6, RN31.6, RN32.6; also elsewhere on the board
HK1: RN3.8; also elsewhere on the board
HK2: RN3.9; also elsewhere on the board
HK3: RN3.10; also elsewhere on the board
HK4: RN6.5; also elsewhere on the board
HK5: RN6.6; also elsewhere on the board
HK6: RN6.7; also elsewhere on the board
HK7: RN6.8; also elsewhere on the board
HLT: RN3.7; also elsewhere on the board
HLTM: RN2.9; also elsewhere on the board
IAK_VM: RN2.3; also elsewhere on the board
INIT: RN1.2; also elsewhere on the board
IRQ0: RN3.3; also elsewhere on the board
IRQ1: RN3.4; also elsewhere on the board
IRQ2: RN3.5; also elsewhere on the board
IRQ3: RN3.6; also elsewhere on the board
unnamed: C45.+, D1.2 (A2), JP61.1
unnamed: Q3.2 (B), R19.1, R20.2
RPLY: RN20.5; also elsewhere on the board
RPLY_VM: RN19.3; also elsewhere on the board
SACK: RN19.5; also elsewhere on the board
SEL: RN1.4; also elsewhere on the board
SRAM_CE2: Q3.3 (C), R12.2; also elsewhere on the board
SRAM_CE_G: R19.2; also elsewhere on the board
SSPARE_SEL: RN15.4, RN31.4; also elsewhere on the board
SSYNC: RN19.2; also elsewhere on the board
SYNC: RN6.4; also elsewhere on the board
TA: RN1.5; also elsewhere on the board
UMAP_VM: RN1.6; also elsewhere on the board
WO: RN2.5; also elsewhere on the board
WTBT: RN20.6; also elsewhere on the board
WTBT_VM: RN2.2; also elsewhere on the board

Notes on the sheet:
EXB-F6WT07G
